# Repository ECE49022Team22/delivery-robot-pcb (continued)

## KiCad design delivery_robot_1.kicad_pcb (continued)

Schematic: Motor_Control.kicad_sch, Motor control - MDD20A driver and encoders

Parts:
C34, C35, C50, C51: 100nF; C_0805_2012Metric
C41, C42: 100nF / 50V X7R; C_0805_2012Metric; MPN C0805C104K5RACTU
C43, C44, C45, C46: 1nF / 50V C0G; C_0805_2012Metric; MPN C0805C102J5GACTU
C47, C48: 1uF / 16V X7R; C_0805_2012Metric; MPN GRM21BR71C105KA01L
F8, F9, F10, F11: 0.2A hold; Fuse_1206_3216Metric; MPN MF-NSMF020X-2
J6: MDD20A PWM1/DIR1/GND; TerminalBlock_Phoenix_MKDS-1,5-3_1x03_P5.00mm_Horizontal; Rating 17.5 A / 250 V (IEC), 26-14 AWG; this d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; MPN 1715035 (MKDS 1,5/3, 5.0 mm pitch)
J7: Motor1 encoder; JST_XH_S4B-XH-A_1x04_P2.50mm_Horizontal; Rating 3 A per contact; MPN S4B-XH-A(LF)(SN)
J15: Motor2 encoder; JST_XH_S4B-XH-A_1x04_P2.50mm_Horizontal; Rating 3 A per contact; MPN S4B-XH-A(LF)(SN)
J16: MDD20A PWM2/DIR2/GND; TerminalBlock_Phoenix_MKDS-1,5-3_1x03_P5.00mm_Horizontal; Rating 17.5 A / 250 V (IEC), 26-14 AWG; this d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; MPN 1715035 (MKDS 1,5/3, 5.0 mm pitch)
R26, R27, R30, R31: 100; R_0805_2012Metric
R28, R29, R32, R33: 1k; R_0805_2012Metric
R52, R53: 10k; R_0805_2012Metric
U6, U7, U11, U12: USBLC6-2SC6; SOT-23-6; MPN USBLC6-2SC6
U9, U10: 74LVC2G17; SOT-23-6; MPN SN74LVC2G17DBVR

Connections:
+3V3: C34.1, C41.1, C42.1, C50.1, U6.5 (VBUS), U9.5 (VCC), U10.5 (VCC), U11.5 (VBUS); also elsewhere on the board
+5V_SYS: C35.1, C51.1, F8.1, F9.1, U7.5 (VBUS), U12.5 (VBUS); also elsewhere on the board
/Motor Control/ENC1_5V: C47.1, F8.2, J7.1
/Motor Control/ENC1_A_CONN: J7.3, R28.2, U7.1 (I/O1), U7.6 (I/O4)
/Motor Control/ENC1_A_F: C43.1, R28.1, U9.1
/Motor Control/ENC1_B_CONN: J7.4, R29.2, U7.3 (I/O2), U7.4 (I/O3)
/Motor Control/ENC1_B_F: C44.1, R29.1, U9.3
/Motor Control/ENC2_5V: C48.1, F9.2, J15.1
/Motor Control/ENC2_A_CONN: J15.3, R32.2, U12.1 (I/O1), U12.6 (I/O1)
/Motor Control/ENC2_A_F: C45.1, R32.1, U10.1
/Motor Control/ENC2_B_CONN: J15.4, R33.2, U12.3 (I/O2), U12.4 (I/O2)
/Motor Control/ENC2_B_F: C46.1, R33.1, U10.3
/Motor Control/M1_DRV_GND: F10.1, J6.3
/Motor Control/M2_DRV_GND: F11.1, J16.3
/Motor Control/MOTOR1_DIR_CONN: J6.2, R27.2, U6.3 (I/O2), U6.4 (I/O3)
/Motor Control/MOTOR1_PWM_CONN: J6.1, R26.2, R52.1, U6.1 (I/O1), U6.6 (I/O4)
/Motor Control/MOTOR2_DIR_CONN: J16.2, R31.2, U11.3 (I/O2), U11.4 (I/O2)
/Motor Control/MOTOR2_PWM_CONN: J16.1, R30.2, R53.1, U11.1 (I/O1), U11.6 (I/O1)
ENC1_A: U9.6; also elsewhere on the board
ENC1_B: U9.4; also elsewhere on the board
ENC2_A: U10.6; also elsewhere on the board
ENC2_B: U10.4; also elsewhere on the board
GND: C34.2, C35.2, C41.2, C42.2, C43.2, C44.2, C45.2, C46.2, C47.2, C48.2, C50.2, C51.2, F10.2, F11.2, J7.2, J15.2, R52.2, R53.2, U6.2 (GND), U7.2 (GND), U9.2 (GND), U10.2 (GND), U11.2 (GND), U12.2 (GND); also elsewhere on the board
MOTOR1_DIR: R27.1; also elsewhere on the board
MOTOR1_PWM: R26.1; also elsewhere on the board
MOTOR2_DIR: R31.1; also elsewhere on the board
MOTOR2_PWM: R30.1; also elsewhere on the board

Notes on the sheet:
ESD arrays - one per connector: U6 J6, U11 J16, U7 J7, U12 J15
Encoder supply and motor-driver line protection (If the am-3651 outputs turn out to be open-collector, bodge 4.7k from each A/B line to its ENCn_5V.)
Motor control - Cytron MDD20A dual-channel driver + two AndyMark PG27 motors with am-3651 encoders
Off-board connectors
STM32F091 PIN ASSIGNMENT series R connector MOTOR1_PWM PA6 TIM3_CH1 R26 100R J6 pin 1 -> MDD20A PWM1 (R52 10k pull-down) MOTOR1_DIR PB0 GPIO R27 100R J6 pin 2 -> MDD20A DIR1 ENC1_A PA15 TIM2_CH1 U9 <- R28 1k J7 pin 3 <- encoder A ENC1_B PB3 TIM2_CH2 U9 <- R29 1k J7 pin 4 <- encoder B MOTOR2_PWM PA7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
Series resistors (MCU side): 100R driver lines, 1k encoder lines
Encoder input buffers - 74LVC2G17 on +3V3 (inputs tolerate 5.5 V, even unpowered)

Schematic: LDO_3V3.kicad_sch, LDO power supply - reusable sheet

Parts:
C24: 1uF / 16V X7R; C_0805_2012Metric; MPN GRM21BR71C105KA01L
C25: 10uF / 10V X7R; C_0805_2012Metric; MPN C2012X7R1A106K125AC
C26, C27: 10nF / 100V X7R; C_0805_2012Metric; MPN GRM21BR72A103KA01L
R8: 35.7k / 0.1%; R_0805_2012Metric; MPN TBD
R9: 11.5k / 1%; R_0805_2012Metric; MPN TBD
U4: TPS7A8101DRBR; TI_DRB0008A_VSON8_3x3mm; MPN TPS7A8101DRBR

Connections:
+3V3: C25.1, C27.1, R8.1, U4.1 (OUT), U4.2 (OUT); also elsewhere on the board
+5V_SYS: C24.1, U4.5 (EN), U4.7 (IN), U4.8 (IN); also elsewhere on the board
GND: C24.2, C25.2, C26.2, R9.2, U4.4 (GND), U4.9 (EP); also elsewhere on the board
unnamed: C27.2, R8.2, R9.1, U4.3 (FB)
unnamed: C26.1, U4.6 (NR)

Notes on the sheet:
VOUT nominal = 0.8 x (1 + 35.7k / 11.5k) = 3.284 V (E96 values) 1 A is the TOTAL output budget for the STM32 and other 3.3 V loads.
Reusable sheet: VIN_5V input, VOUT_3V3 output, common GND
C25: require >= 4.7 uF EFFECTIVE capacitance; selected part modeled at 8.8 uF. EN tied to IN. C26 (NR) and C27 (bypass across R8) are 10 nF: start-up about 1.7 ms (TI tests the part with CNR = 10 nF, CBYPASS = 0). 470 nF gave 80 ms, during which 5 V encoder and servo signals could reach MCU pins wh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
5 V motor / encoder supply branches BEFORE this sheet.
Layout: capacitors close to U4; EP pad 9 to GND copper and thermal vias. Heat: the real 3.3 V load is about 150 mA, about 0.25 W at 5 V input (1.7 W only at the full 1 A rating).
5 V to 3.3 V LDO supply

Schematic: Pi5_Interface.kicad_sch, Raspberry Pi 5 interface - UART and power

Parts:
D15: BAT54WS; D_SOD-323; MPN BAT54WS-E3-18
J13: Pi 5 link; JST_XH_S6B-XH-A_1x06_P2.50mm_Horizontal; MPN S6B-XH-A(LF)(SN)
J14: Pi 5 power; TerminalBlock_Phoenix_MKDS-1,5-2_1x02_P5.00mm_Horizontal; Rating 17.5 A / 250 V (IEC), 26-14 AWG; used a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; MPN 1715022 (MKDS 1,5/2, 5.0 mm pitch)
Q2: DMN63D8L; SOT-23; MPN DMN63D8L-7
R12, R13, R47: 1k; R_0805_2012Metric
R46: 100k; R_0805_2012Metric
TP1: +5V_PI; TestPoint_Keystone_5000-5004_Miniature; MPN 5000 (red miniature test loop)

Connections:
+5V_PI: J14.1, TP1.1 (1_1); also elsewhere on the board
/Pi 5 Interface/PI_3V3: D15.2 (A), J13.4
/Pi 5 Interface/PI_BOOT0: J13.6, R47.1
/Pi 5 Interface/PI_RESET: J13.5, Q2.1 (G), R46.1
/Pi 5 Interface/PI_RXD: J13.2, R12.2
/Pi 5 Interface/PI_TXD: J13.1, R13.2
AUX_EN: D15.1 (K); also elsewhere on the board
BOOT: R47.2; also elsewhere on the board
GND: J13.3, J14.2, Q2.2 (S), R46.2; also elsewhere on the board
NRST: Q2.3 (D); also elsewhere on the board
USART2_RX: R13.1; also elsewhere on the board
USART2_TX: R12.1; also elsewhere on the board

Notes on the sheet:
J13 1 <- Pi GPIO14 TXD J13 2 -> Pi GPIO15 RXD J13 3 = GND (Pi header pin 6); 3.3 V logic R12/R13 near U1 (no ESD array fitted)
Raspberry Pi 5 link (USART2, PA2 TX / PA3 RX), Pi 3V3 sense, STM32 reset and BOOT0
Bring-up: leave J14 unwired, check TP1; load-test J14; then connect the Pi. 5-6 A path
Pi 5 power: +5V_PI -> J14 USB-C pigtail (no fuse: U2's current limit and hiccup protect it)
Pi-controlled functions (J13 4 <- Pi 3V3 pin 1, 5 <- GPIO23 pin 16, 6 <- GPIO24 pin 18) AUX_EN: the +5V_AUX buck (U5) runs only while the Pi's 3V3 is up. PI_RESET + PI_BOOT0 -> reflash the STM32 from the Pi over USART2 (AN2606: PA2/PA3 is a bootloader port on STM32F09x). Sequence: BOOT0 high, pulse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

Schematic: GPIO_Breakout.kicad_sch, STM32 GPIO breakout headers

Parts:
J8: Expansion header; PinHeader_2x08_P2.54mm_Vertical

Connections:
+3V3: J8.1; also elsewhere on the board
GND: J8.2, J8.16; also elsewhere on the board
PA1: J8.4; also elsewhere on the board
PA4: J8.5; also elsewhere on the board
PB6: J8.13; also elsewhere on the board
PB7: J8.14; also elsewhere on the board
PB9: J8.15; also elsewhere on the board
PB13: J8.7; also elsewhere on the board
PB15: J8.8; also elsewhere on the board
PC0: J8.3; also elsewhere on the board
PC2: J8.6; also elsewhere on the board
PC6: J8.9; also elsewhere on the board
PC7: J8.10; also elsewhere on the board
PC10: J8.11; also elsewhere on the board
PC11: J8.12; also elsewhere on the board

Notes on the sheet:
MCU expansion header J8 - 2.54 mm male pins, spare MCU pins only SPI2: PB13 SCK, PC2 MISO, PB15 MOSI, PB9 CS | I2C1: PB6 SCL, PB7 SDA (no pull-ups on board) USART3: PC10 TX, PC11 RX | ADC: PC0, PA1, PA4 (DAC) | PWM: PC6, PC7 (TIM3)

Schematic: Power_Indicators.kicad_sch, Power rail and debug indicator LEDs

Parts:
D3, D4, D5, D6, D7: GREEN; LED_0805_2012Metric; MPN LTST-C170KGKT
D8, D9, D11: YELLOW; LED_0805_2012Metric; MPN LTST-C170KSKT
R3: 511; R_0805_2012Metric
R17: 4.75k; R_0805_2012Metric
R18, R19, R20: 1.5k; R_0805_2012Metric
R21, R22, R24: 681; R_0805_2012Metric

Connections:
+3V3: R3.1; also elsewhere on the board
+5V_AUX: R19.1; also elsewhere on the board
+5V_PI: R18.1; also elsewhere on the board
+5V_SYS: R20.1; also elsewhere on the board
+12V: R17.1; also elsewhere on the board
GND: D3.1 (K), D4.1 (K), D5.1 (K), D6.1 (K), D7.1 (K), D8.1 (K), D9.1 (K), D11.1 (K); also elsewhere on the board
LED_MOTOR: R24.1; also elsewhere on the board
LED_PI_LINK: R22.1; also elsewhere on the board
LED_USER: R21.1; also elsewhere on the board
unnamed: D3.2 (A), R3.2
unnamed: D4.2 (A), R17.2
unnamed: D5.2 (A), R18.2
unnamed: D6.2 (A), R19.2
unnamed: D7.2 (A), R20.2
unnamed: D8.2 (A), R21.2
unnamed: D9.2 (A), R22.2
unnamed: D11.2 (A), R24.2

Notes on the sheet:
LED current ~2-2.7 mA: R = (Vrail - 2.0 V) / I. +12V uses 4.75k for the 10.8-14.6 V battery range. All resistors 0805; worst-case dissipation 34 mW (R17 at 14.6 V).
PA5 LED_USER: heartbeat PB12 LED_PI_LINK: Pi UART activity PB14 LED_MOTOR: motor running / fault 681R: (3.3 - 2.1) / 681 = 1.8 mA per pin
Power rail indicators - one green LED per rail (Lite-On LTST-C190KGKT, 0603, Vf 2.0 V typ)
Debug LEDs - STM32 GPIO, active high (Lite-On LTST-C190KSKT yellow, 0603)

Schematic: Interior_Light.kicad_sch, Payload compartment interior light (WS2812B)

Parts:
C54, C56: 100nF / 50V X7R; C_0805_2012Metric; MPN C0805C104K5RACTU
C55: 10uF / 16V X7R; C_0805_2012Metric; MPN CL21B106KOQNNNE
D16: D5V0L1B2WS; D_SOD-323; MPN D5V0L1B2WS-7
F12: 1.5A hold; Fuse_1812_4532Metric; MPN 1812L150/16DR
J24: INTERIOR LIGHT; JST_XH_B3B-XH-A_1x03_P2.50mm_Vertical; MPN B3B-XH-A(LF)(SN)
R59: 100k; R_0805_2012Metric; Tolerance 1%; MPN RC0805FR-07100KL
R60: 330; R_0805_2012Metric; Tolerance 1%; MPN RC0805FR-07330RL
U14: SN74LV1T125DBVR; SOT-23-5; MPN SN74LV1T125DBVR

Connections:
+5V_AUX: C54.1, F12.1, U14.5 (VCC); also elsewhere on the board
/Interior Light/LIGHT_5V: C55.1, C56.1, F12.2, J24.1
/Interior Light/LIGHT_DIN: D16.2 (A2), J24.2, R60.2
/Interior Light/LIGHT_DIN_BUF: R60.1, U14.4 (Y)
GND: C54.2, C55.2, C56.2, D16.1 (A1), J24.3, R59.2, U14.1 (~OE), U14.3 (GND); also elsewhere on the board
LIGHT_DATA: R59.1, U14.2 (A); also elsewhere on the board

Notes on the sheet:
S17.2: the light turns on within 0.5 s of the lid opening and off within 2 s of it closing. Off-board WS2812B strip, up to 16 LEDs; firmware caps its draw at 0.5 A. Power: +5V_AUX through F12 (1.5 A PTC, same part as the AUX ports), so the light is only powered while the Pi is up. Off-board: put a 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
Payload compartment interior light - WS2812B strip (S17.2)

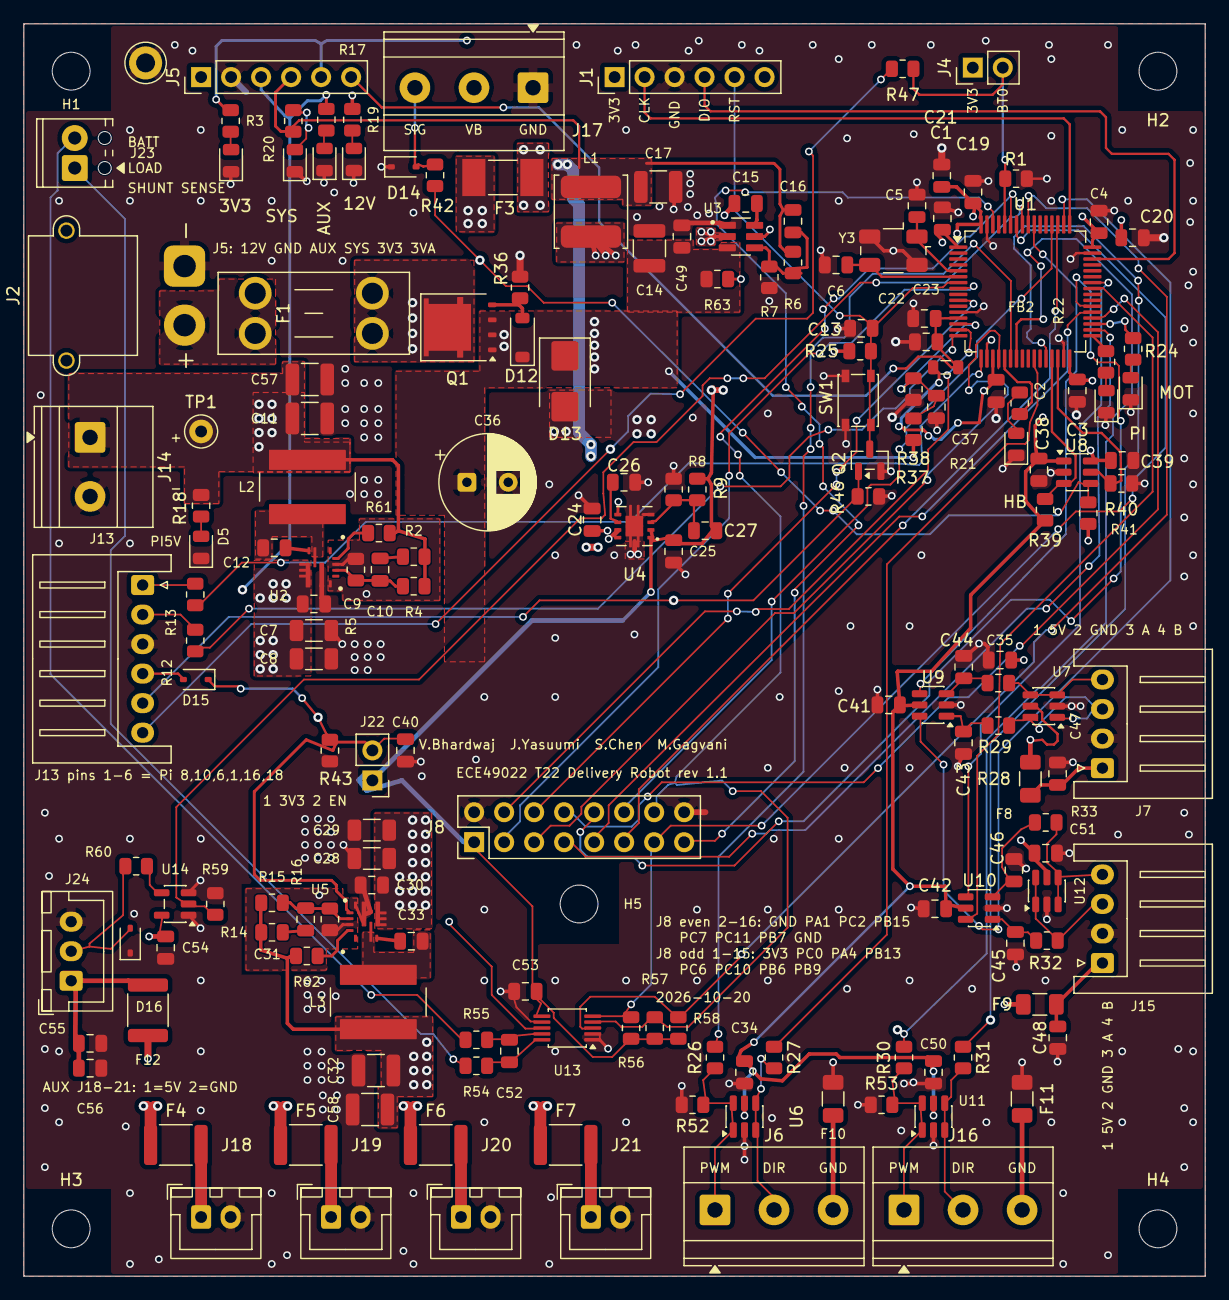
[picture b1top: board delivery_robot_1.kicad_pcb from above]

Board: 4 copper layers, 100.0 x 106.0 mm, 181 parts (0 on the bottom side), 107 nets.

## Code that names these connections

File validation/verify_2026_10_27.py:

"""Verify the 2026-10-27 battery monitor / interior light change against the pre-change netlist.

Usage (from the repository root):
    kicad-cli sch export netlist --format kicadxml -o /tmp/before.xml delivery_robot_1.kicad_sch   # on the parent commit
    kicad-cli sch export netlist --format kicadxml -o system-netlist.xml delivery_robot_1.kicad_sch
    python validation/verify_2026_10_27.py [before.xml] [after.xml]
"""
from pathlib import Path
import sys
import xml.etree.ElementTree as ET

repo = Path(__file__).resolve().parent.parent
before_path = Path(sys.argv[1]) if len(sys.argv) > 1 else Path('/tmp/before.xml')
after_path = Path(sys.argv[2]) if len(sys.argv) > 2 else repo / 'system-netlist.xml'
old = ET.parse(before_path).getroot()
new = ET.parse(after_path).getroot()


def nets(root):
    return {n.attrib['name']: {(x.attrib['ref'], x.attrib['pin']) for x in n.findall('node')}
            for n in root.findall('./nets/net')}


def pin_map(net_map):
    return {node: name for name, nodes in net_map.items() for node in nodes}


def comps(root):
    out = {}
    for c in root.findall('./components/comp'):
        fields = {f.attrib['name']: (f.text or '') for f in c.findall('./fields/field')}
        out[c.attrib['ref']] = {'value': c.findtext('value'), 'footprint': c.findtext('footprint'), **fields}
    return out


a, b = nets(old), nets(new)
pa, pb = pin_map(a), pin_map(b)
ca, cb = comps(old), comps(new)
failures = []
passes = 0


def check(cond, msg):
    global passes
    if cond:
        passes += 1
    else:
        failures.append(msg)


BM = '/Battery Monitor/'
IL = '/Interior Light/'

# Pin -> net pairs from the two connection tables
expected = {
    # Change 1: battery current monitor
    ('J23', '1'): BM + 'SH_LOAD', ('R54', '1'): BM + 'SH_LOAD',
    ('R54', '2'): BM + 'INA_INP', ('U13', '10'): BM + 'INA_INP', ('C52', '1'): BM + 'INA_INP',
    ('J23', '2'): BM + 'SH_BATT', ('R55', '1'): BM + 'SH_BATT',
    ('R55', '2'): BM + 'INA_INN', ('U13', '9'): BM + 'INA_INN', ('C52', '2'): BM + 'INA_INN',
    ('U13', '6'): '+3V3', ('C53', '1'): '+3V3', ('C53', '2'): 'GND',
    ('U13', '7'): 'GND',
    ('U13', '8'): '+12V',
    ('U13', '2'): 'GND', ('U13', '1'): 'GND',
    ('U13', '5'): 'PB6', ('U13', '4'): 'PB7',
    ('R56', '2'): 'PB6', ('R56', '1'): '+3V3',
    ('R57', '2'): 'PB7', ('R57', '1'): '+3V3',
    ('U13', '3'): 'BATT_ALERT', ('R58', '2'): 'BATT_ALERT', ('R58', '1'): '+3V3',
    ('U1', '56'): 'BATT_ALERT',
    # Change 2: interior light
    ('U1', '57'): 'LIGHT_DATA', ('R59', '1'): 'LIGHT_DATA', ('R59', '2'): 'GND', ('U14', '2'): 'LIGHT_DATA',
    ('U14', '1'): 'GND',
    ('U14', '5'): '+5V_AUX', ('C54', '1'): '+5V_AUX', ('C54', '2'): 'GND',
    ('U14', '3'): 'GND',
    ('U14', '4'): IL + 'LIGHT_DIN_BUF', ('R60', '1'): IL + 'LIGHT_DIN_BUF',
    ('R60', '2'): IL + 'LIGHT_DIN', ('J24', '2'): IL + 'LIGHT_DIN',
    ('F12', '1'): '+5V_AUX', ('F12', '2'): IL + 'LIGHT_5V',
    ('J24', '1'): IL + 'LIGHT_5V', ('C55', '1'): IL + 'LIGHT_5V', ('C56', '1'): IL + 'LIGHT_5V',
    ('C55', '2'): 'GND', ('C56', '2'): 'GND',
    ('J24', '3'): 'GND',
}
for node, net in expected.items():
    check(pb.get(node) == net, f'{node[0]} pin {node[1]}: expected {net}, got {pb.get(node)}')

# D16 is bidirectional: one pin on LIGHT_DIN, the other on GND
check({pb.get(('D16', '1')), pb.get(('D16', '2'))} == {IL + 'LIGHT_DIN', 'GND'},
      f"D16: expected LIGHT_DIN / GND, got {pb.get(('D16', '1'))} / {pb.get(('D16', '2'))}")

# Shunt-sense nets carry nothing else (in particular, no GND tie at the inputs)
exact = {
    BM + 'SH_LOAD': {('J23', '1'), ('R54', '1')},
    BM + 'SH_BATT': {('J23', '2'), ('R55', '1')},
    BM + 'INA_INP': {('R54', '2'), ('U13', '10'), ('C52', '1')},
    BM + 'INA_INN': {('R55', '2'), ('U13', '9'), ('C52', '2')},
    'BATT_ALERT': {('U13', '3'), ('R58', '2'), ('U1', '56')},
    'LIGHT_DATA': {('U1', '57'), ('R59', '1'), ('U14', '2')},
    IL + 'LIGHT_DIN_BUF': {('U14', '4'), ('R60', '1')},
    IL + 'LIGHT_5V': {('F12', '2'), ('J24', '1'), ('C55', '1'), ('C56', '1')},
}
for net, nodes in exact.items():
    check(b.get(net) == nodes, f'{net}: expected {sorted(nodes)}, got {sorted(b.get(net, ()))}')
check(b.get(IL + 'LIGHT_DIN', set()) - {('D16', '1'), ('D16', '2')} == {('R60', '2'), ('J24', '2')},
      f"{IL}LIGHT_DIN: unexpected members {sorted(b.get(IL + 'LIGHT_DIN', ()))}")

# PB6 / PB7 gained exactly U13 plus its pull-up
check(b['PB6'] - a['PB6'] == {('U13', '5'), ('R56', '2')}, f"PB6 gained {sorted(b['PB6'] - a['PB6'])}")
check(b['PB7'] - a['PB7'] == {('U13', '4'), ('R57', '2')}, f"PB7 gained {sorted(b['PB7'] - a['PB7'])}")
check(a['PB6'] <= b['PB6'] and a['PB7'] <= b['PB7'], 'PB6/PB7 lost a pre-existing pin (J8 13/14, U1 58/59)')

# No pre-existing component pin changed nets, except U1 pins 56 and 57
allowed = {('U1', '56'), ('U1', '57')}
for node, net in pa.items():
    if node in allowed:
        continue
    check(pb.get(node) == net, f'pre-existing {node[0]} pin {node[1]} moved: {net} -> {pb.get(node)}')
check(pa[('U1', '56')].startswith('unconnected-') and pa[('U1', '57')].startswith('unconnected-'),
      'U1 pins 56/57 were not no-connect in the baseline')

# No net lost a pre-existing pin (the two U1 no-connect nets are the only ones allowed to vanish)
for net, nodes in a.items():
    if nodes <= allowed:
        continue
    check(nodes <= b.get(net, set()), f'net {net} lost {sorted(nodes - b.get(net, set()))}')

# Pre-existing parts unchanged (value, footprint, Manufacturer, MPN)
for ref, f in ca.items():
    g = cb.get(ref)
    check(g is not None, f'{ref} missing')
    if g:
        for k in ('value', 'footprint', 'Manufacturer', 'MPN'):
            check(f.get(k) == g.get(k), f'{ref} {k} changed: {f.get(k)!r} -> {g.get(k)!r}')

# New references: exactly the 18 parts, unique, Manufacturer and MPN filled, footprints as specified
new_parts = {
    'U13': 'Package_SO:TSSOP-10_3x3mm_P0.5mm',
    'J23': 'TerminalBlock_Phoenix:TerminalBlock_Phoenix_MPT-0,5-2-2.54_1x02_P2.54mm_Horizontal',
    'U14': 'Package_TO_SOT_SMD:SOT-23-5',
    'J24': 'Connector_JST:JST_XH_B3B-XH-A_1x03_P2.50mm_Vertical',
    'F12': 'Fuse:Fuse_1812_4532Metric',
    'D16': 'Diode_SMD:D_SOD-323',
    **{f'R{n}': 'Resistor_SMD:R_0805_2012Metric' for n in range(54, 61)},
    **{f'C{n}': 'Capacitor_SMD:C_0805_2012Metric' for n in range(52, 57)},
}
refs = [c.attrib['ref'] for c in new.findall('./components/comp')]
check(len(refs) == len(set(refs)), 'duplicate references in the new netlist')
added = set(cb) - set(ca)
check(added == set(new_parts), f'added parts {sorted(added)} != expected {sorted(new_parts)}')
for ref, fp in new_parts.items():
    g = cb.get(ref, {})
    check(bool(g.get('Manufacturer')) and bool(g.get('MPN')), f'{ref}: Manufacturer/MPN missing')
    check(bool(g.get('Datasheet')) and g.get('Datasheet') != '~' and bool(g.get('Description')),
          f'{ref}: Datasheet/Description missing')
    check(g.get('footprint') == fp, f"{ref}: footprint {g.get('footprint')} != {fp}")

if failures:
    print(f'FAIL: {len(failures)} of {passes + len(failures)} checks failed')
    for f in failures:
        print('  -', f)
    sys.exit(1)
print(f'PASS: {passes} checks. Both connection tables match pin for pin; INA_INP/INA_INN carry no GND tie; '
      f'PB6/PB7 gained exactly U13 + R56/R57; no pre-existing pin moved except U1 56/57; no net lost a pin; '
      f'{len(ca)} existing parts unchanged; {len(added)} new parts unique with Manufacturer, MPN, Datasheet, '
      f'Description and the specified footprints.')
